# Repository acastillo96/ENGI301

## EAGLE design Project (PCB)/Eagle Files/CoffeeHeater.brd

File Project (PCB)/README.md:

# PCB Project
This directory contains all the files to make the PCB for the Coffee Heater Project

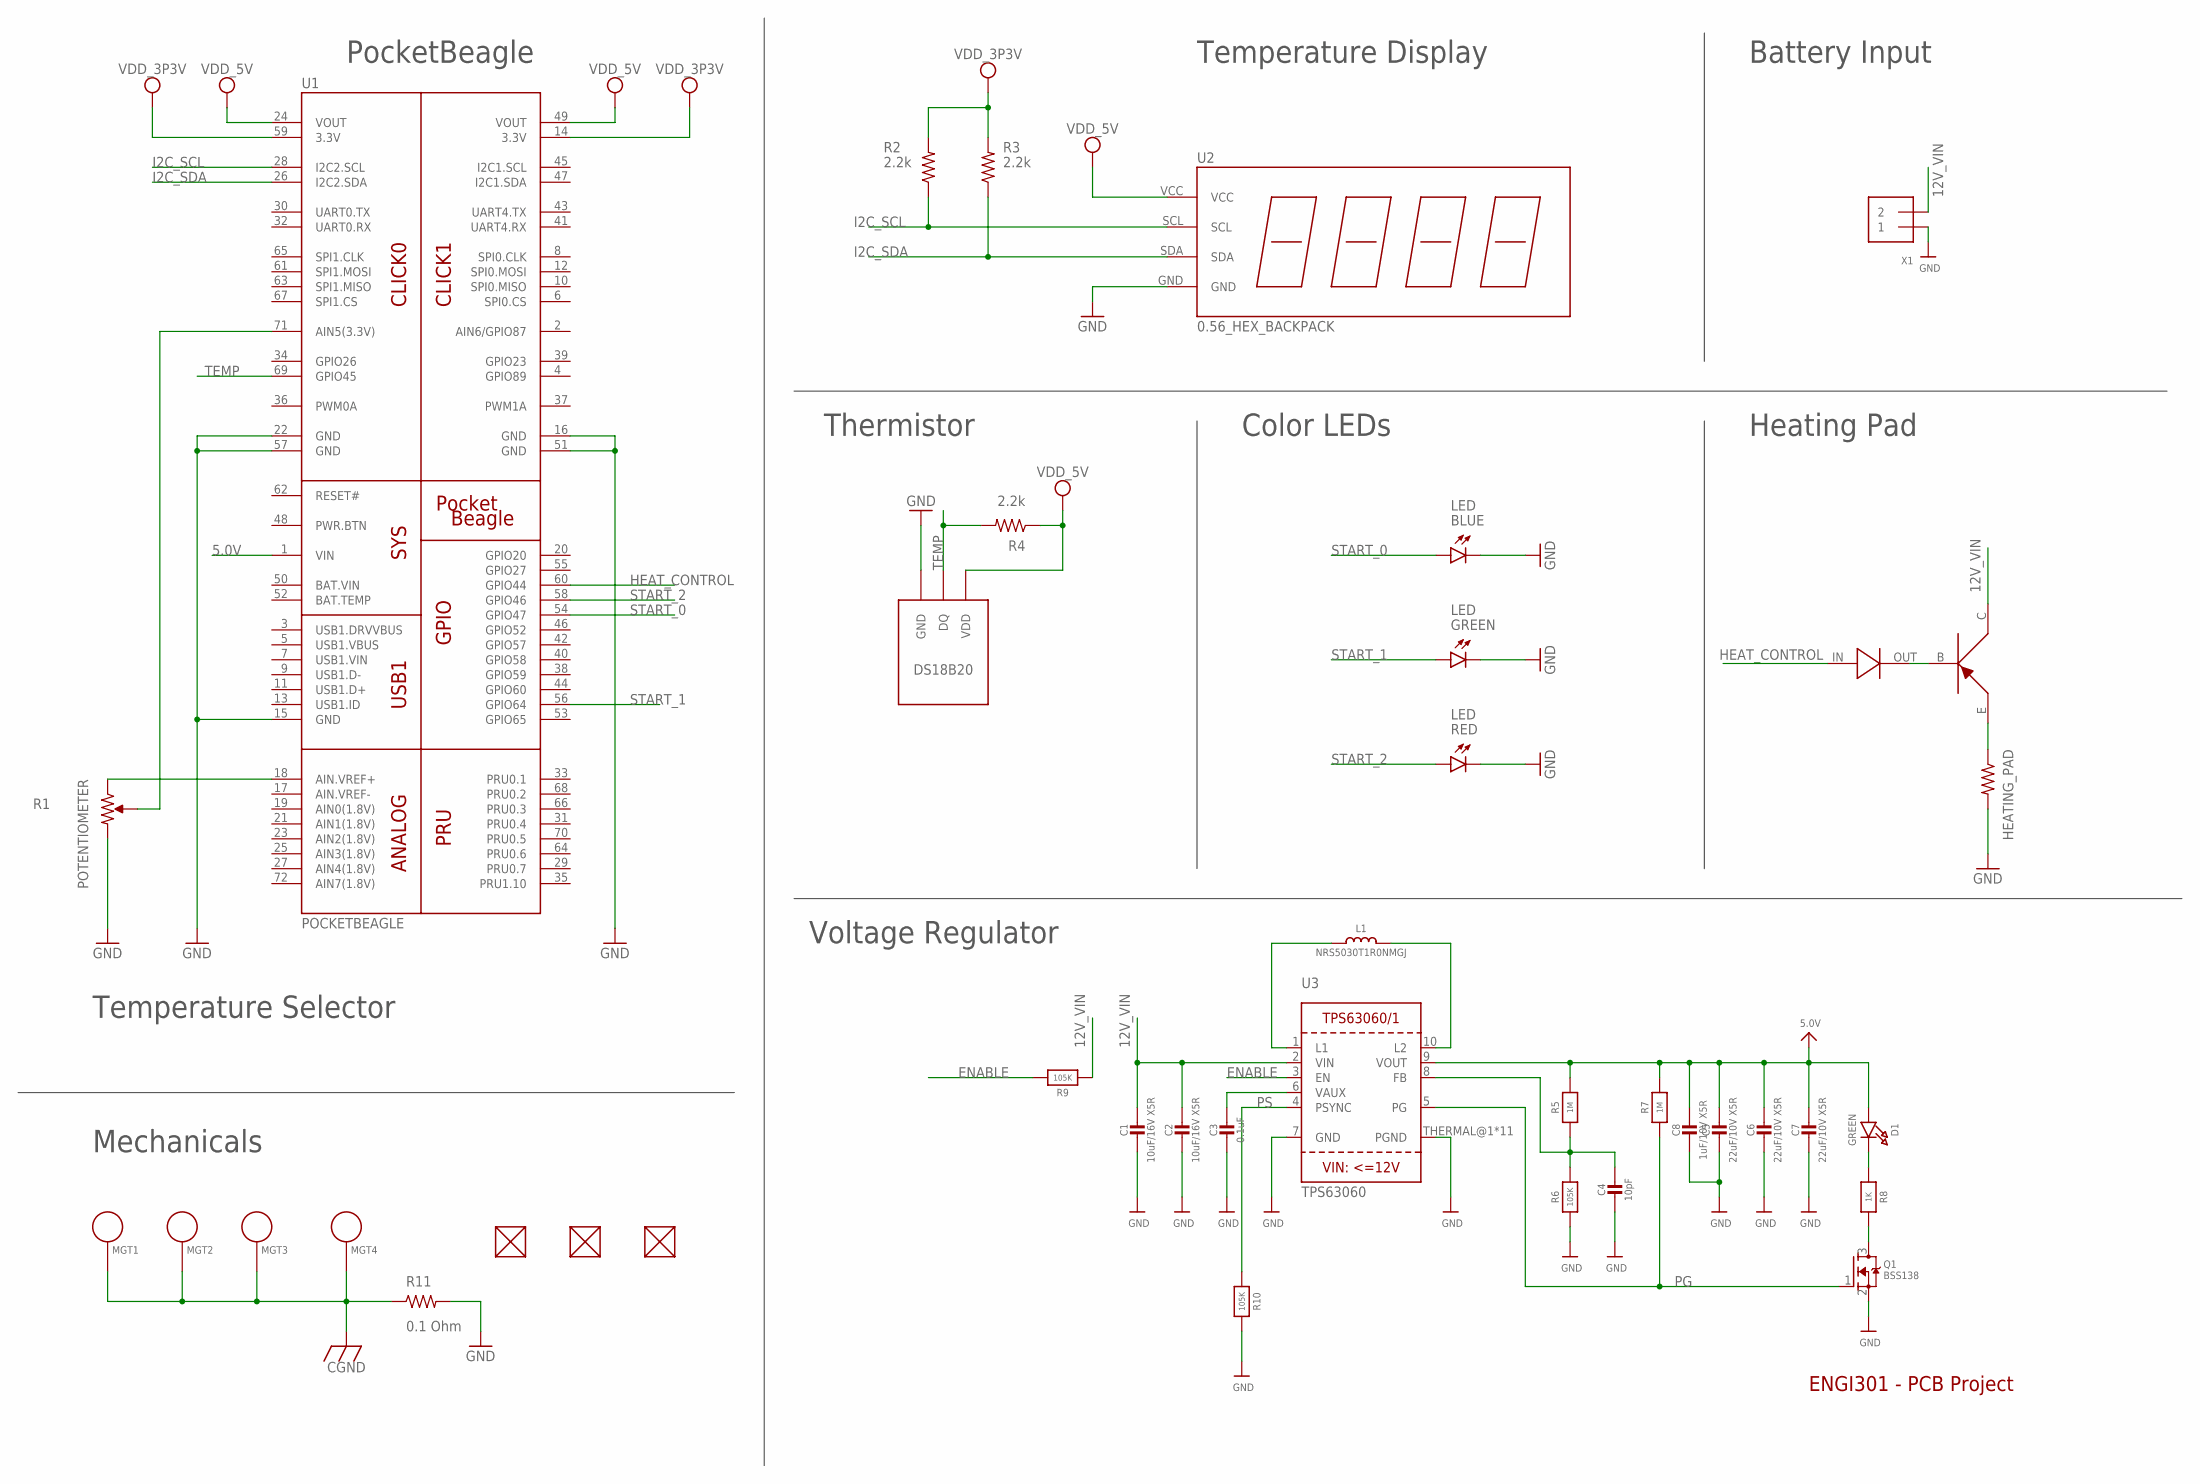
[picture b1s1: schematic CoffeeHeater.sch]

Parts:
BLUE: LED; EIA-STD
C1, C2: 10uF/16V X5R; 0805-NO
C3: 0.1uF; 0805-NO
C4: 10pF; 0805-NO
C5, C6, C7: 22uF/10V X5R; 0805-NO
C8: 1uF/10V X5R; 0805-NO
D1: GREEN; CHIPLED_0805_NOOUTLINE
D2: DIODE
FUD1, FUD2, FUD3: FIDUCIAL; FIDUCIAL_40MIL
GREEN: LED; EIA-STD
H1: HEATING_PAD
L1: NRS5030T1R0NMGJ; INDUCTOR_5X5MM_TDK_VLC5045
MGT1, MGT2, MGT3, MGT4: MOUNTING_HOLE
Q1: BSS138; SOT23-WIDE
R1: POTENTIOMETER; POT-PO90S
R2, R3, R4: 2.2k; R0603
R5, R7: 1M; 0805-NO
R6, R9, R10: 105K; 0805-NO
R8: 1K; 0805-NO
R11: 0.1 Ohm; R0805
RED: LED; EIA-STD
T1: DS18B20_TEMP_SENSOR
TR1: TIP32C_TRANSISTOR
U1: POCKETBEAGLE
U2: 0.56_HEX_BACKPACK
U3: TPS63060; PWSON-N10
X1: TERMBLOCK_1X2; TERMBLOCK_1X2-3.5MM

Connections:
5.0V: C5.1, C6.1, C7.1, C8.1, D1.A, R5.2, R7.2, U1.1 (VIN), U3.9 (VOUT)
12V_VIN: C1.1, C2.1, R9.1, TR1.C, U3.2 (VIN), X1.2
BASE: D2.OUT, TR1.B
BAT.VIN: U1.50 (BAT.VIN)
CGND: MGT1.P$1, MGT2.P$1, MGT3.P$1, MGT4.P$1, R11.1
ENABLE: R9.2, U3.3 (EN)
GND: BLUE.P$2 (C), C1.2, C2.2, C3.2, C4.2, C5.2, C6.2, C7.2, C8.2, GREEN.P$2 (C), H1.GND (2), Q1.2 (S), R1.CW, R6.1, R10.2, R11.2, RED.P$2 (C), T1.GND, U1.15 (GND), U1.16 (GND), U1.22 (GND), U1.51 (GND), U1.57 (GND), U2.GND, U3.7 (GND), U3.THERMAL@1 (PGND), U3.THERMAL@5 (PGND), U3.THERMAL@6 (PGND), U3.THERMAL@7 (PGND), U3.THERMAL@8 (PGND), U3.THERMAL@9 (PGND), U3.THERMAL@10 (PGND), U3.THERMAL@11 (PGND), U3.THERMAL@12 (PGND), U3.THERMAL@13 (PGND), U3.THERMAL@14 (PGND), X1.1
HEAT_CONTROL: D2.IN, U1.60 (GPIO44)
I2C_SCL: R2.1, U1.28 (I2C2.SCL), U2.SCL
I2C_SDA: R3.1, U1.26 (I2C2.SDA), U2.SDA
unnamed: H1.VDD (1), TR1.E
unnamed: R1.CCW, U1.18 (AIN.VREF+)
unnamed: R1.S, U1.71 (AIN5(3.3V))
unnamed: L1.P$1 (1), U3.1 (L1)
unnamed: L1.P$2 (2), U3.10 (L2)
unnamed: C3.1, U3.6 (VAUX)
unnamed: C4.1, R5.1, R6.2, U3.8 (FB)
unnamed: D1.C, R8.1
unnamed: Q1.3 (D), R8.2
PG: Q1.1 (G), R7.1, U3.5 (PG)
PS: R10.1, U3.4 (PSYNC)
START_0: BLUE.P$1 (A), U1.54 (GPIO47)
START_1: GREEN.P$1 (A), U1.56 (GPIO64)
START_2: RED.P$1 (A), U1.58 (GPIO46)
TEMP: R4.2, T1.DQ, U1.69 (GPIO45)
VDD_3P3V: R2.2, R3.2, U1.14 (3.3V), U1.59 (3.3V)
VDD_5V: R4.1, T1.VDD, U1.24 (VOUT), U1.49 (VOUT), U2.VCC

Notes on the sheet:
ENGI301 - PCB Project
Temperature Display
Thermistor
Color LEDs
Heating Pad
PocketBeagle
Temperature Selector
Voltage Regulator
Battery Input
Mechanicals

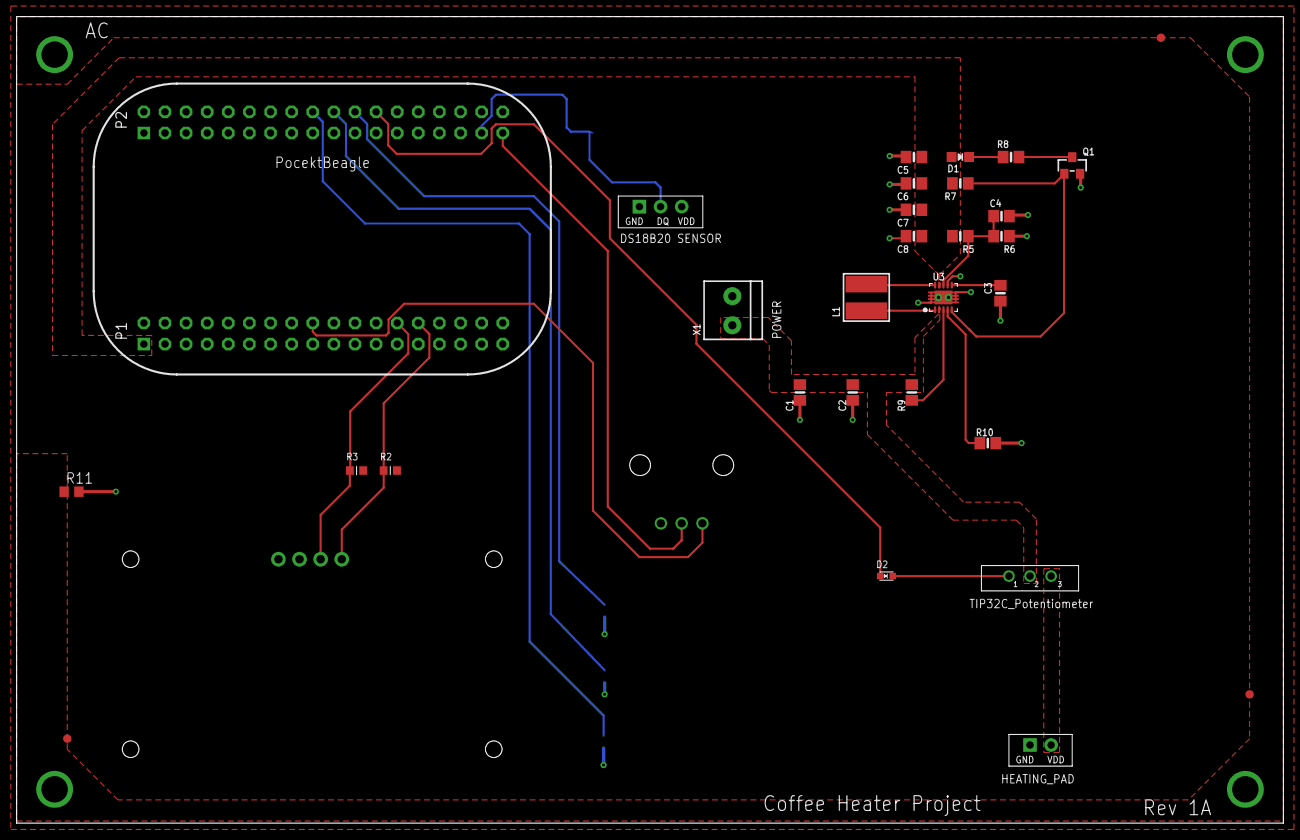
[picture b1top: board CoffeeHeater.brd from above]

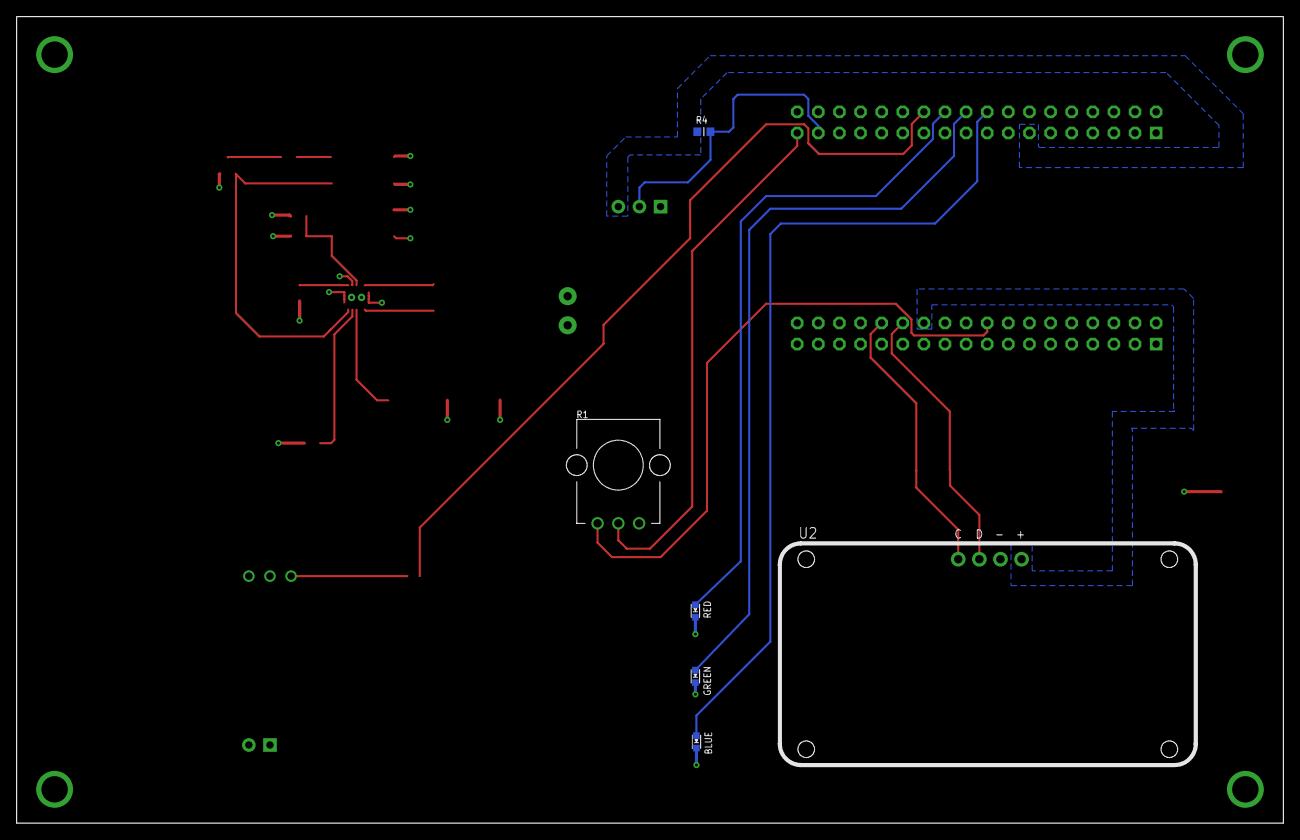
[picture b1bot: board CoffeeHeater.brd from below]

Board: 2 copper layers, 152.4 x 97.0 mm, 40 parts (6 on the bottom side), 26 nets.

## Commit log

2018-09-26 Adding first calculator
2018-09-26 Updated the calculator to include more operators and compatibility with Python2
2018-09-27 First version of program that turns the USR3 LED on and off
2018-09-27 Edited the sleep time.
2018-09-27 Update to the program.
2018-10-12 Created the project folder and uploaded the description
2018-11-14 Made some updates on the Fritzing diagram and connected my GitHub to SourceTree
2018-11-14 Deleted duplicate files
2018-11-19 Added the first version of the library, schematics, and board. Uploaded the Project Proposal.
2018-11-28 Updated the library with all the devices and made progress in the schematics and the board
2018-11-28 Minor updates to the general layout
2018-12-02 Started routing some of the connections
2018-12-07 Connect all the GND nets
2018-12-10 Added all of the connections
2018-12-10 Added mechanical parts and updated routes.
2018-12-10 Added the Gerber files and the pdf of the schematics. Finalized the layout.
2018-12-10 Re-ordered the Eagle files.
2018-12-11 Updated connections
2018-12-11 Updated library and created BOM
2018-12-12 Fixed pours and fixed gerber files
2018-12-12 Screenshots for all the different layers

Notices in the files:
parts and their libraries:
microbuilder: This work is placed in the public domain, and may be freely used for commercial and non-commercial work with the following conditions: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
